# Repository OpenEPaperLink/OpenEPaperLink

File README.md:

# OpenEPaperLink

This is an alternative firmware and protocol for the multiple Electronic Shelf Labels. It can be used to set up E-Paper tags and supply them with content.

The software in this project consists of two parts: Accesspoint-firmware and Tag firmware.
Additionally, there are various hardware designs for accesspoints and flasher-interfaces to program the tags, preferably using programming jigs

>[!Note]
>Please refer to the [Wiki](https://github.com/jjwbruijn/OpenEPaperLink/wiki) for the latest information.
>
>Much of this README is now obsolete, but it has been retained for historical reference.
>
>For example the use of tags as RF coprocessors is no longer supported.
 
## Aims
- Low power (currently around 9µA with a minimum of 40 second latency)
- Even lower power when there's no AP around
- Low latency (tags can check for new data every 40 seconds)
- High transfer speeds - It can do about 5kbyte/s in favorable RF conditions. This allows for lower power
- RF-friendly - We don't need to acknowledge EVERY packet, and we don't need to transfer data we already have

## What is required to set up OpenEPaperLink

On the [Wiki](https://github.com/jjwbruijn/OpenEPaperLink/wiki) there is a ton of information regarding all kinds of tags and building the access points.

The entire setup requires a few tags and an ESP32. A tag is used as an 802.15.4 radio for the ESP32. You'll need a ZBS_Flasher in order to flash the tags. Using the 'mac' option on ZBS_Flasher makes sure a tag flashed with a custom firmware has a valid mac address; it uses the stock mac address assigned to the tag if it hasn't been flashed before. If you want to set it yourself, you can edit the mac address in the infopage.

You can hook the AP tag up to the ESP32 with mod wires or a flex PCB. The esp will flash the AP firmware to the Tag automatically. In some cases, a power off/on cycle is required. Please check the serial console output for status information.

After programming the ESP32, make sure to also program the filesystem. This will upload the 'data' folder to the ESP32, with the webinterface.

## OpenEPaperLink Parts and links
* [Mini AP](https://github.com/OpenEPaperLink/Hardware/tree/main/OpenEPaperLink%20Mini%20AP)
* [Combined Flasher and AP](https://github.com/OpenEPaperLink/Hardware/tree/main/OpenEPaperLink%20AP%20and%20Flasher)
* [ATC1441's ZBS flasher page](https://github.com/atc1441/ZBS_Flasher)
* [Tags specs](https://github.com/jjwbruijn/OpenEPaperLink/wiki#tags)
* [Tags troubleshooting](https://github.com/jjwbruijn/OpenEPaperLink/wiki/Troubleshooting-Tags)

## The protocol explained
- The tag checks in with the AP every 40+ seconds. Actual check-in interval is highly dependent on RF conditions, or if the AP tells the tag to delay the next check-in
- The AP holds a list with tag MACs that have pending transfers.
- If a tag checks in, the AP replies with either no data, or information about a pending transfer
- The tag checks if this information is already downloaded to EEPROM, or is already displayed. If this is the case, the transfer is immediately cancelled by issuing a 'transfer complete' packet to the AP.
- The tag then proceeds to request data in 'blocks' of 4096 bytes. The AP responds with an ACK on the request, and specifies how long it will take to gather the data. The tag sleeps until the AP will send the data
- The AP requests its block-buffer to be filled by the ESP32, specifying MD5 and blockID
- Datablock is sent by the AP, which will take about 42 packets for a full block. The tag will keep track of which blocks it has seen
- After a block has been received with missing parts, the tag will request the same block, with a bitmask of blocks that are missing
- The AP responds with the parts as requested by the tag. If there aren't too many blocks requested, the AP will fill the block with duplicate parts, to increase the chance of a successful transmission
- After a full block has been received, the tag will do a simple checksum over all received data. If the checksum matches, the 4K of data is stored in EEPROM storage for later use
- The tag will now either request the next block, or do a full re-request if the checksum failed
- If all blocks are received, the tag will send a 'transfer complete'. 
- The AP will report the completed transfer to the ESP32, and removes the pendingData for this transfer from the queue

## Known issues:
- Some tags work better as APs than others. Your range may suck. The boards on these tags are tiny and fragile. For instance, a dab of hot-glue on a board is enough to warp it pretty severely, and will damage the components that are soldered on there. Reportedly, segmented-display Solum tags work well. 

## Hints and excuses:
- There is no warranty whatsoever. Nothing. Not implied or otherwise suggested. This code isn't fit for anything. Please don't use this code to do nasty things.
- Do a ```make clean``` between buildings for different boards. It really helps!
- This repo builds on SDCC 4.2.0 for Linux. Different SDCC versions can behave VERY differently.  Source sdcc/setup.sh to setup build a local copy and use it for compiling.
- We are happy and honored to see your pull requests! But please, no code/indent style changes :)

## Credits
### Large parts of this repo are based on code written by, and wouldn't be possible without the hard work of:
- dmitry.gr
- atc1441

Hats off to these legends!
 
## Automated Builds
- After a PR gets merged to the main branch, the changed code will be compiled.
- On release, files are added to enable OTA

## License
[Creative Commons Attribution-NonCommercial-ShareAlike 4.0 International (CC BY-NC-SA 4.0)](https://creativecommons.org/licenses/by-nc-sa/4.0/)

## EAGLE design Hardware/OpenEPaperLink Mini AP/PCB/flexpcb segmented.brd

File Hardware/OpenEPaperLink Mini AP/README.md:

# OpenEPaperLink Mini-AP #

A small OpenEPaperLink AP, using an ESP32-S2 and a segmented tag

* [How to build one](https://github.com/jjwbruijn/OpenEPaperLink/blob/master/Hardware/OpenEPaperLink%20Mini%20AP/Building.md)

* [How to use one](https://github.com/jjwbruijn/OpenEPaperLink/blob/master/Hardware/OpenEPaperLink%20Mini%20AP/Getting%20Started.md)

* [Case](https://github.com/jjwbruijn/OpenEPaperLink/tree/master/Hardware/OpenEPaperLink%20Mini%20AP/Case)
                                                                                                                                                                                                                                                                                                                                                        
* [PCB](https://github.com/jjwbruijn/OpenEPaperLink/tree/master/Hardware/OpenEPaperLink%20Mini%20AP/PCB)

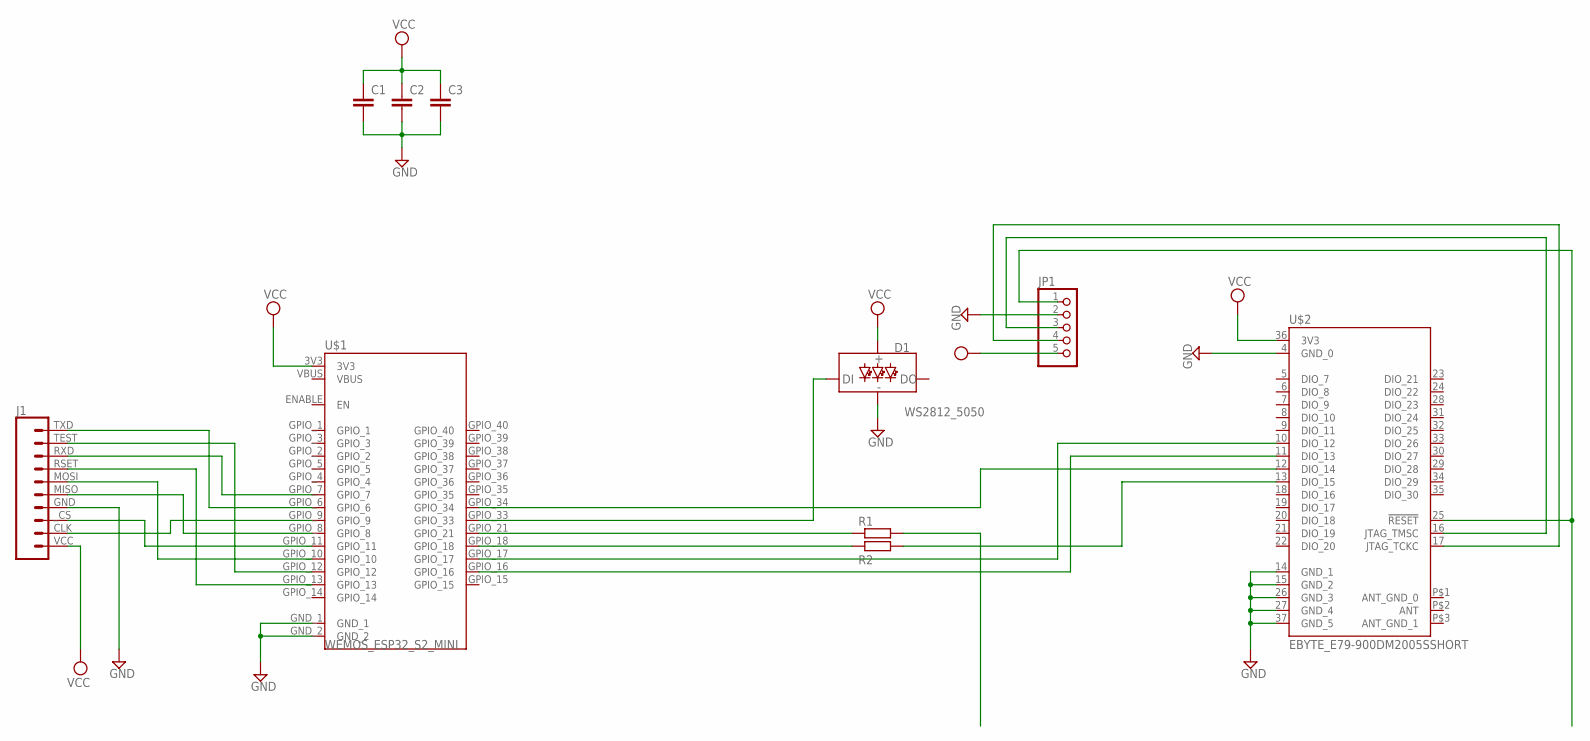
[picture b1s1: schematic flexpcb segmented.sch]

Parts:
C1, C2, C3: C-EUC1206; C1206
D1: WS2812_5050; WS2812-5X5-4PIN
J1: SOLUM_ZBS_DEBUGSEGMENTED_DISPLAY; SOLUM_ZBS_DEBUG_SEG
JP1: PINHD-1X55X2MM; 1_05X2MM
R1, R2: R-EU_R0805; R0805
U$1: WEMOS_ESP32_S2_MINI
U$2: EBYTE_E79-900DM2005SSHORT; EBYTE_E79-900DM2005S_PARTIAL

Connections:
ANT: U$2.P$2 (ANT)
ANT_GND_0: U$2.P$1 (ANT_GND_0)
ANT_GND_1: U$2.P$3 (ANT_GND_1)
GND: C1.2, C2.2, C3.2, D1.GND, J1.GND (4), JP1.2, U$1.GND_1, U$1.GND_2, U$2.4 (GND_0), U$2.14 (GND_1), U$2.15 (GND_2), U$2.26 (GND_3), U$2.27 (GND_4), U$2.37 (GND_5)
unnamed: JP1.1, U$2.25 (!RESET)
unnamed: R1.1, U$1.GPIO_21
unnamed: R2.2, U$2.13 (DIO_15)
unnamed: R2.1, U$1.GPIO_18
unnamed: U$1.GPIO_34, U$2.12 (DIO_14)
unnamed: U$1.GPIO_16, U$2.11 (DIO_13)
unnamed: U$1.GPIO_17, U$2.10 (DIO_12)
unnamed: D1.DI, U$1.GPIO_33
unnamed: JP1.3, U$2.16 (JTAG_TMSC)
unnamed: JP1.4, U$2.17 (JTAG_TCKC)
unnamed: J1.TEST (9), U$1.GPIO_12
unnamed: J1.RSET (7), U$1.GPIO_13
unnamed: J1._CS (3), U$1.GPIO_11
unnamed: J1.MOSI (6), U$1.GPIO_10
unnamed: J1.CLK (2), U$1.GPIO_9
unnamed: J1.RXD (8), U$1.GPIO_7
unnamed: J1.TXD (10), U$1.GPIO_6
unnamed: J1.MISO (5), U$1.GPIO_8
VBUS: U$1.VBUS
VCC: C1.1, C2.1, C3.1, D1.VCC, J1.VCC (1), JP1.5, U$1.3V3, U$2.36 (3V3)

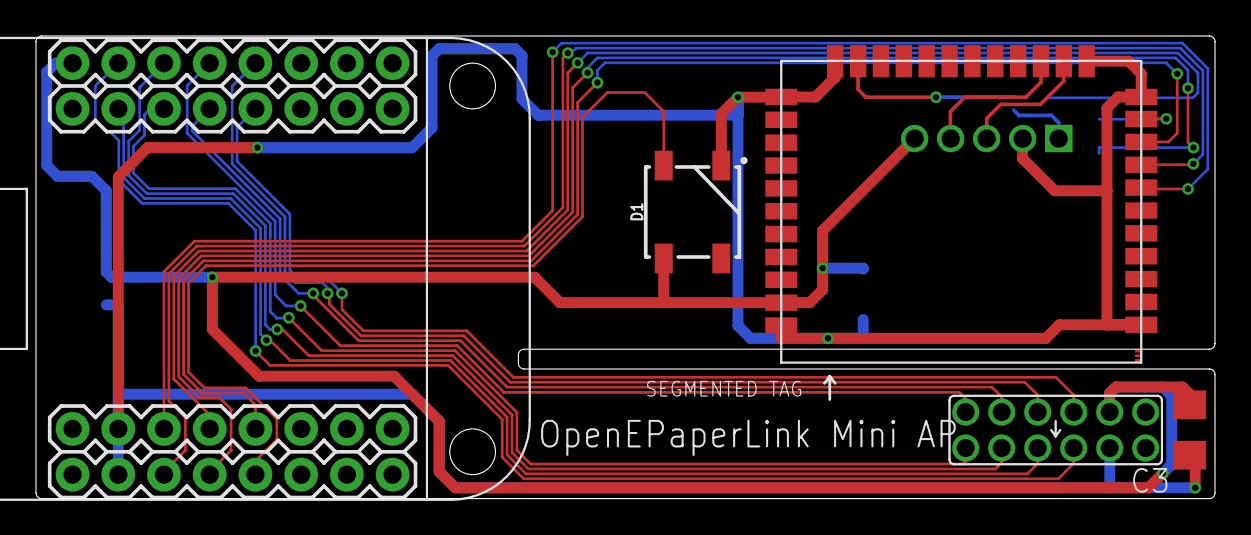
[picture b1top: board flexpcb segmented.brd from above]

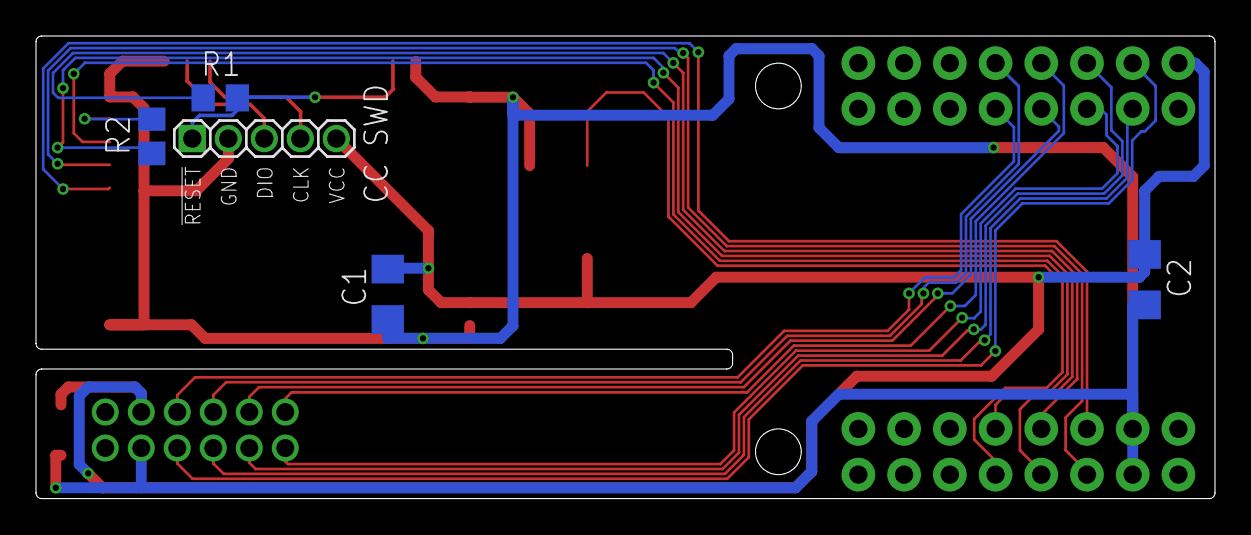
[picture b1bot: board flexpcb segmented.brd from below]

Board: 2 copper layers, 65.5 x 25.7 mm, 10 parts (5 on the bottom side), 20 nets.

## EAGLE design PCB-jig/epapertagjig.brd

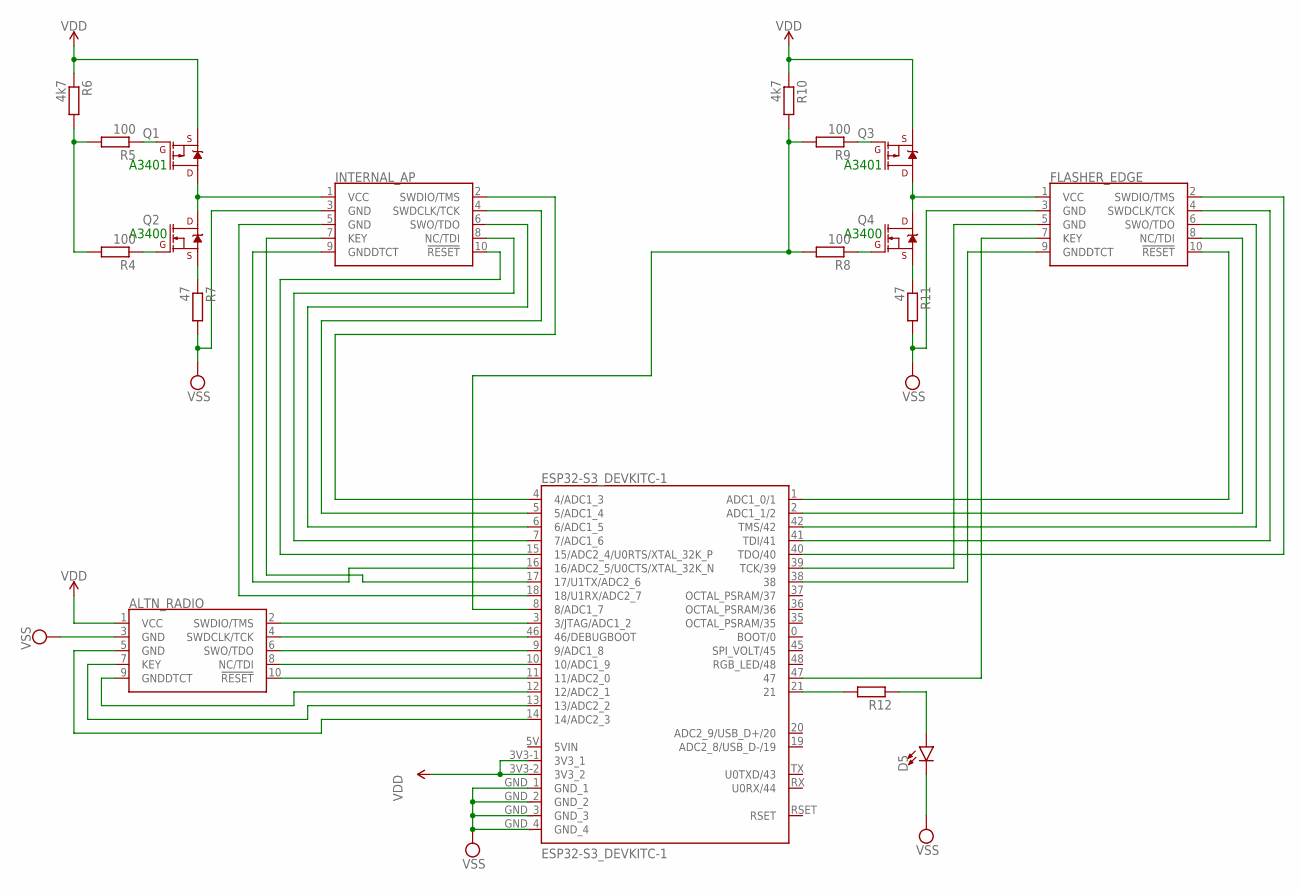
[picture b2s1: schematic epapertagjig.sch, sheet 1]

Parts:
ALTN_RADIO: JTAG; 2X5-SMD-1.27MM
D5: LED1206; LED-1206
FLASHER_EDGE: CORTEX_JTAG_DEBUG_PTH; 2X5-PTH-1.27MM
INTERNAL_AP: JTAG; 2X5-SMD-1.27MM
J9: ESP32-S3_DEVKITC-1
Q1, Q3: 1.1A/60V/600mΩ; SOT23-3
Q2, Q4: 5.8A/30V/35mΩ; SOT23-3
R4, R5, R8, R9: 100; R1206
R6, R10: 4k7; R1206
R7, R11: 47; R1206
R12: R-EU_R1206; R1206

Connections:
unnamed: INTERNAL_AP.1 (VCC), Q1.3 (D), Q2.3 (D)
unnamed: Q2.2 (S), R7.1
unnamed: R4.2, R5.2, R6.2
unnamed: Q2.1 (G), R4.1
unnamed: Q1.1 (G), R5.1
unnamed: FLASHER_EDGE.1 (VCC), Q3.3 (D), Q4.3 (D)
unnamed: J9.8 (8/ADC1_7), R8.2, R9.2, R10.2
unnamed: Q4.1 (G), R8.1
unnamed: Q3.1 (G), R9.1
unnamed: Q4.2 (S), R11.1
unnamed: INTERNAL_AP.5 (GND), J9.18 (18/U1RX/ADC2_7)
unnamed: INTERNAL_AP.9 (GNDDTCT), J9.16 (16/ADC2_5/U0CTS/XTAL_32K_N)
unnamed: INTERNAL_AP.10 (!RESET), J9.15 (15/ADC2_4/U0RTS/XTAL_32K_P)
unnamed: INTERNAL_AP.8 (NC/TDI), J9.7 (7/ADC1_6)
unnamed: INTERNAL_AP.6 (SWO/TDO), J9.6 (6/ADC1_5)
unnamed: INTERNAL_AP.4 (SWDCLK/TCK), J9.5 (5/ADC1_4)
unnamed: INTERNAL_AP.2 (SWDIO/TMS), J9.4 (4/ADC1_3)
unnamed: FLASHER_EDGE.6 (SWO/TDO), J9.42 (TMS/42)
unnamed: FLASHER_EDGE.10 (!RESET), J9.1 (ADC1_0/1)
unnamed: FLASHER_EDGE.8 (NC/TDI), J9.2 (ADC1_1/2)
unnamed: FLASHER_EDGE.4 (SWDCLK/TCK), J9.41 (TDI/41)
unnamed: FLASHER_EDGE.2 (SWDIO/TMS), J9.40 (TDO/40)
unnamed: ALTN_RADIO.2 (SWDIO/TMS), J9.3 (3/JTAG/ADC1_2)
unnamed: ALTN_RADIO.4 (SWDCLK/TCK), J9.46 (46/DEBUGBOOT)
unnamed: ALTN_RADIO.6 (SWO/TDO), J9.9 (9/ADC1_8)
unnamed: ALTN_RADIO.8 (NC/TDI), J9.10 (10/ADC1_9)
unnamed: ALTN_RADIO.10 (!RESET), J9.11 (11/ADC2_0)
unnamed: ALTN_RADIO.9 (GNDDTCT), J9.12 (12/ADC2_1)
unnamed: ALTN_RADIO.7 (KEY), J9.13 (13/ADC2_2)
unnamed: ALTN_RADIO.5 (GND), J9.14 (14/ADC2_3)
unnamed: FLASHER_EDGE.5 (GND), J9.39 (TCK/39)
unnamed: FLASHER_EDGE.9 (GNDDTCT), J9.38
unnamed: FLASHER_EDGE.7 (KEY), J9.47
unnamed: INTERNAL_AP.7 (KEY), J9.17 (17/U1TX/ADC2_6)
unnamed: J9.21, R12.2
unnamed: D5.A, R12.1
VDD: ALTN_RADIO.1 (VCC), J9.3V3-1 (3V3_1), J9.3V3-2 (3V3_2), Q1.2 (S), Q3.2 (S), R6.1, R10.1
VSS: ALTN_RADIO.3 (GND), D5.C, FLASHER_EDGE.3 (GND), INTERNAL_AP.3 (GND), J9.GND_1, J9.GND_2, J9.GND_3, J9.GND_4, R7.2, R11.2

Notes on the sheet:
A3401
A3400

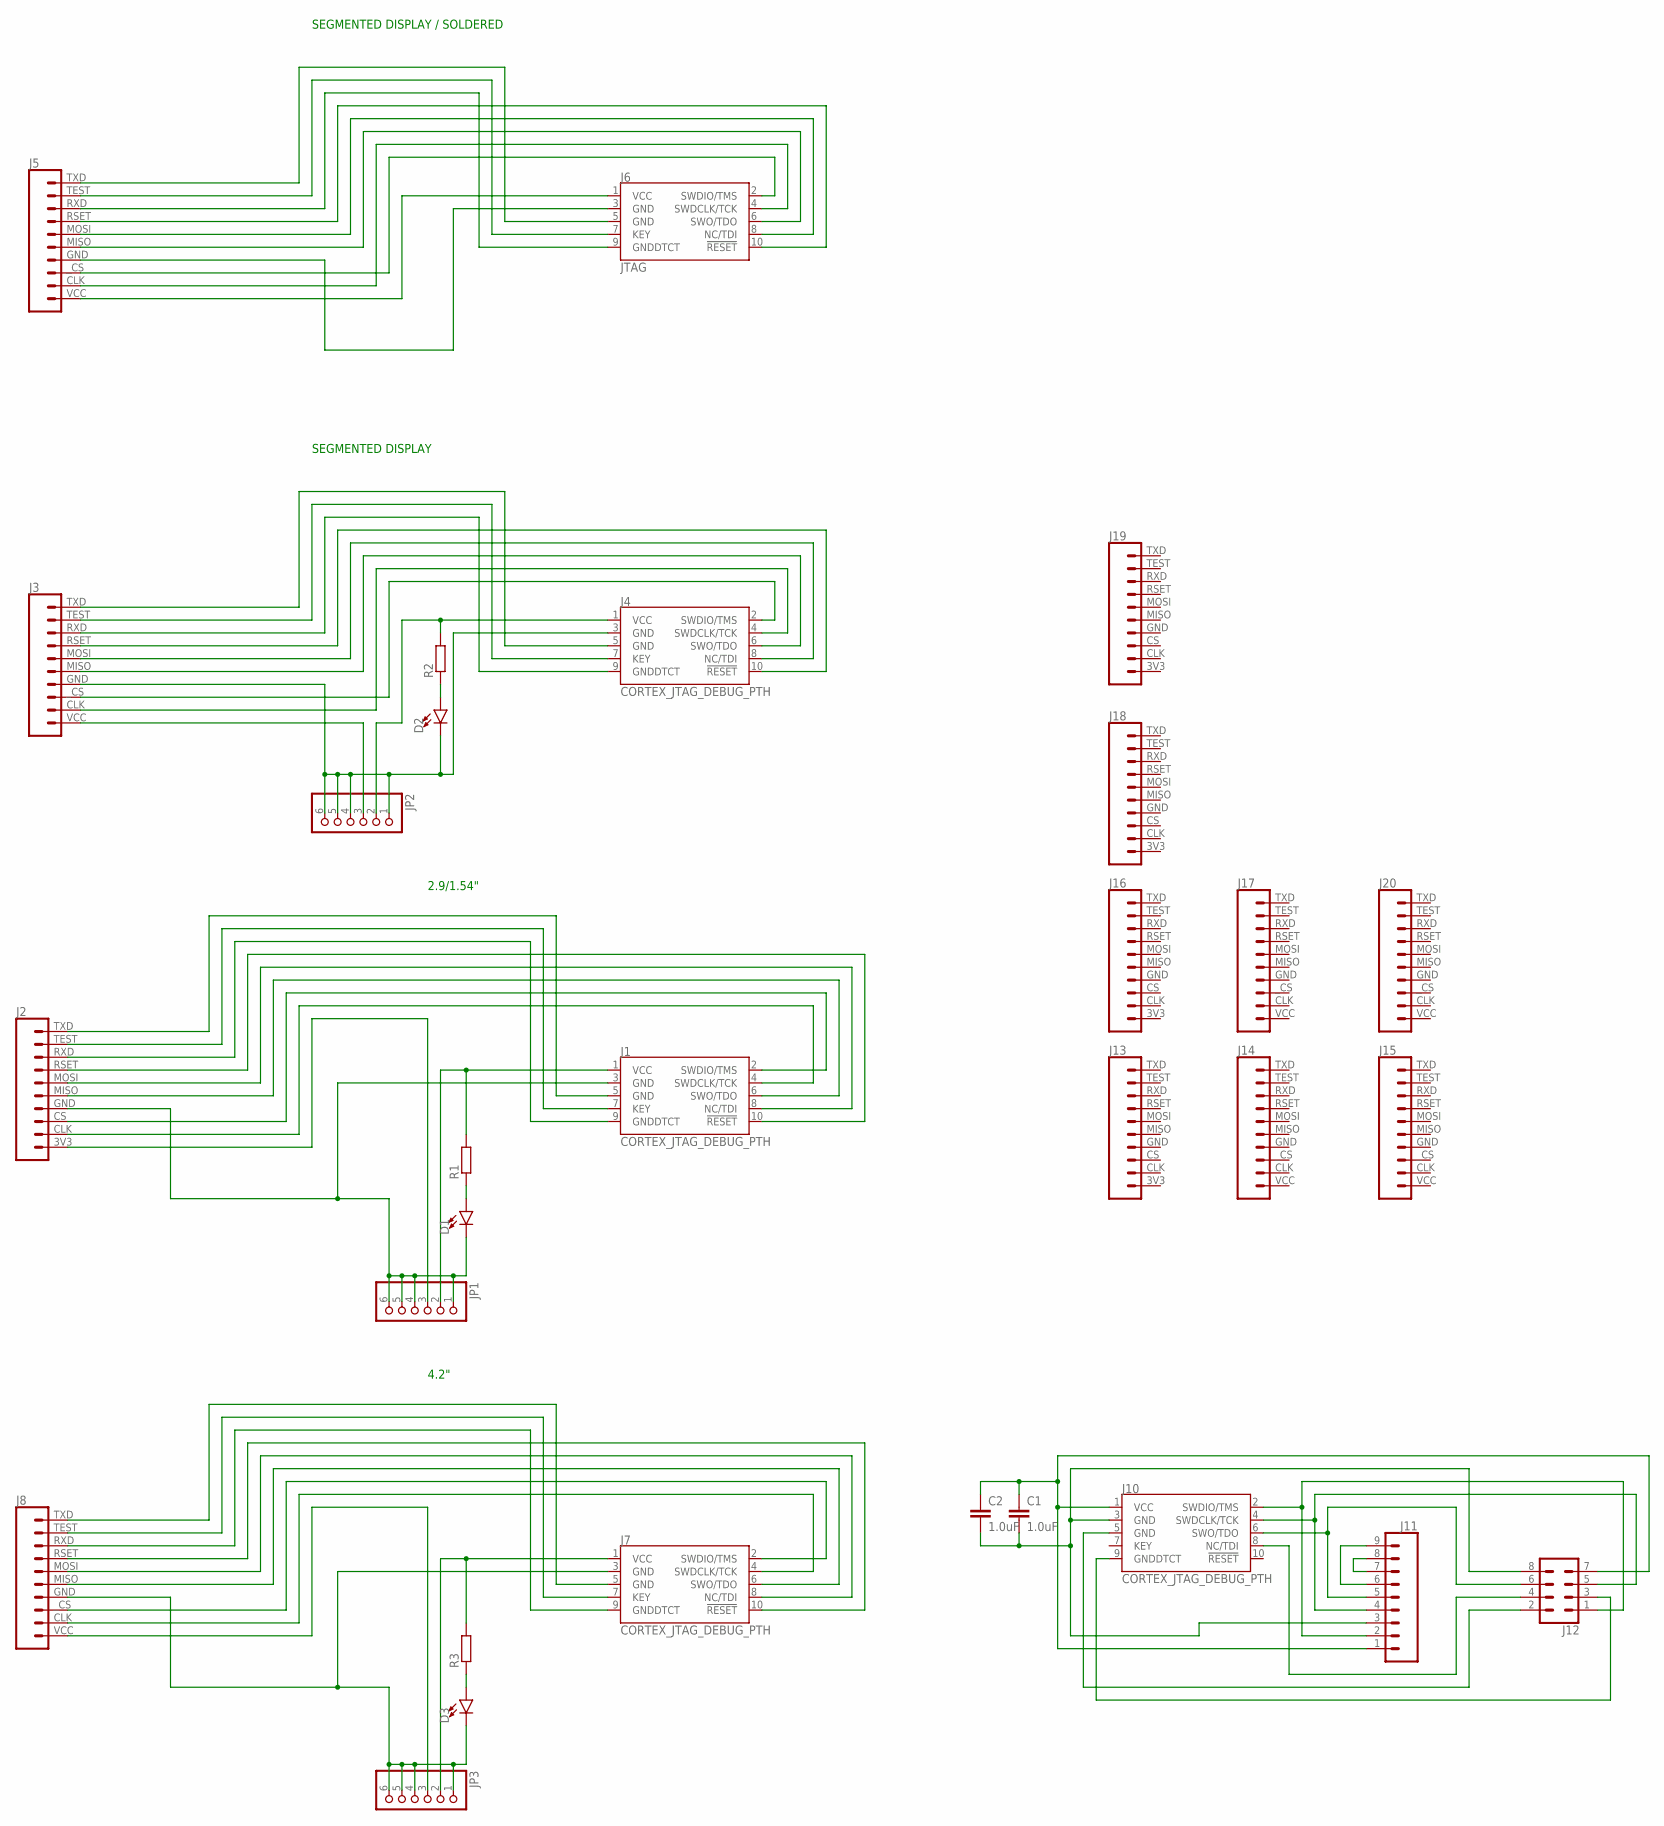
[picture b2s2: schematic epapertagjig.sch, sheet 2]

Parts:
C1, C2: 1.0uF; 1206
D1, D2, D3: LED1206; LED-1206
J1, J4, J7, J10: CORTEX_JTAG_DEBUG_PTH; 2X5-PTH-1.27MM
J2, J13, J16, J18, J19: SOLUM_ZBS_DEBUG
J3, J5, J14, J17: SOLUM_ZBS_DEBUGSEGMENTED_DISPLAY; SOLUM_ZBS_DEBUG_SEG
J6: JTAG; 2X5-SMD-1.27MM
J8, J15, J20: SOLUM_ZBS_DEBUGSOLUM_ZBS_DEBUG_4.2; SOLUM_ZBS_DEBUG_4.2
J11: CONN_09; 1X09
J12: CONN_04X2; 2X4
JP1, JP2, JP3: PINHD-1X6/90; 1X06/90
R1, R2, R3: R-EU_R1206; R1206

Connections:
3V1: J8.VCC (1), JP3.3
3V3: J2.3V3 (1), JP1.3
GND: D1.C, J1.3 (GND), J2.GND (4), JP1.1, JP1.4, JP1.5, JP1.6
GND1: J5.GND (4), J6.3 (GND)
GND2: D2.C, J3.GND (4), J4.3 (GND), JP2.1, JP2.4, JP2.5, JP2.6
GND3: D3.C, J7.3 (GND), J8.GND (4), JP3.1, JP3.4, JP3.5, JP3.6
unnamed: D2.A, R2.1
unnamed: D1.A, R1.1
unnamed: D3.A, R3.1
unnamed: J4.1 (VCC), JP2.2, R2.2
unnamed: J1.4 (SWDCLK/TCK), J2.CLK (2)
unnamed: J1.2 (SWDIO/TMS), J2.CS (3)
unnamed: J1.6 (SWO/TDO), J2.MISO (5)
unnamed: J3._CS (3), J4.2 (SWDIO/TMS)
unnamed: J1.8 (NC/TDI), J2.MOSI (6)
unnamed: J1.10 (!RESET), J2.RSET (7)
unnamed: J1.9 (GNDDTCT), J2.RXD (8)
unnamed: J1.7 (KEY), J2.TEST (9)
unnamed: J1.5 (GND), J2.TXD (10)
unnamed: J3.CLK (2), J4.4 (SWDCLK/TCK)
unnamed: J3.MISO (5), J4.6 (SWO/TDO)
unnamed: J3.MOSI (6), J4.8 (NC/TDI)
unnamed: J3.RSET (7), J4.10 (!RESET)
unnamed: J3.VCC (1), JP2.3
unnamed: J3.RXD (8), J4.9 (GNDDTCT)
unnamed: J3.TEST (9), J4.7 (KEY)
unnamed: J3.TXD (10), J4.5 (GND)
unnamed: J7.4 (SWDCLK/TCK), J8.CLK (2)
unnamed: J5._CS (3), J6.2 (SWDIO/TMS)
unnamed: J5.CLK (2), J6.4 (SWDCLK/TCK)
unnamed: J5.MISO (5), J6.6 (SWO/TDO)
unnamed: J5.MOSI (6), J6.8 (NC/TDI)
unnamed: J5.RSET (7), J6.10 (!RESET)
unnamed: J5.VCC (1), J6.1 (VCC)
unnamed: J5.RXD (8), J6.9 (GNDDTCT)
unnamed: J5.TEST (9), J6.7 (KEY)
unnamed: J5.TXD (10), J6.5 (GND)
unnamed: J7.2 (SWDIO/TMS), J8._CS (3)
unnamed: J7.6 (SWO/TDO), J8.MISO (5)
unnamed: J7.8 (NC/TDI), J8.MOSI (6)
unnamed: J7.10 (!RESET), J8.RSET (7)
unnamed: J7.9 (GNDDTCT), J8.RXD (8)
unnamed: J7.7 (KEY), J8.TEST (9)
unnamed: J7.5 (GND), J8.TXD (10)
unnamed: C1.1, C2.1, J10.1 (VCC), J11.1, J12.7
unnamed: J11.7, J11.8
unnamed: C1.2, C2.2, J10.3 (GND), J11.3, J12.8
unnamed: J11.6, J11.9
unnamed: J10.6 (SWO/TDO), J11.5, J12.6
unnamed: J10.4 (SWDCLK/TCK), J11.4, J12.5
unnamed: J10.2 (SWDIO/TMS), J11.2, J12.1
unnamed: J10.8 (NC/TDI), J12.4
unnamed: J10.5 (GND), J12.2
unnamed: J10.9 (GNDDTCT), J12.3
V_IN: J1.1 (VCC), JP1.2, R1.2
V_IN1: J7.1 (VCC), JP3.2, R3.2

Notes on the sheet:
SEGMENTED DISPLAY
2.9/1.54"
SEGMENTED DISPLAY / SOLDERED
4.2"

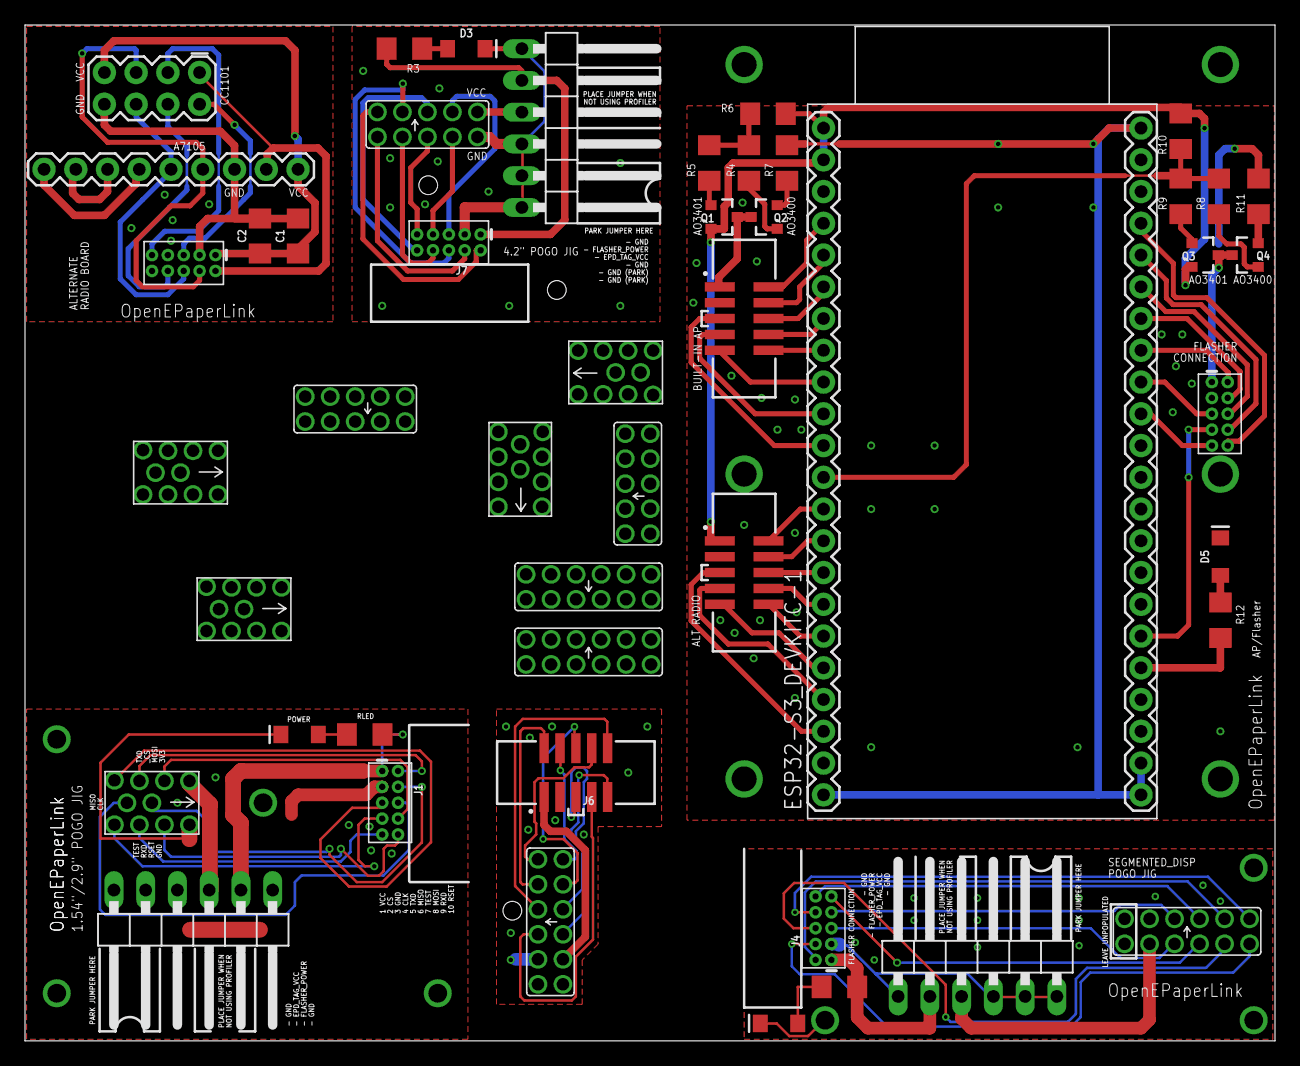
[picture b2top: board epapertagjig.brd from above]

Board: 2 copper layers, 100.0 x 81.3 mm, 48 parts (0 on the bottom side), 94 nets.

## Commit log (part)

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2025-03-24 Avoid error message log print when parsers.json is missing
2025-03-24 Add Ethernet support
    The ethernet support allows to make the network/internet connection
    via LAN cable instead of WiFi. LAN is preferred, if a LAN cable is
    connected and a valid IP configuration via DHCP can be obtained, WiFi
    is switched off. If the LAN cable is disconnected, a fall back to
    WiFi is done.
    Use those defines in platform.ini for PHY settings:
2025-03-24 Add OpenEPaperLink_ESP32-PoE-ISO_AP to release build
2025-03-25 Added support for Elecrow C6 wireless module.
2025-03-25 Added optional (compile time) debug logging to C6 & H2.
2025-03-25 Added support for Elcrow Advanced 2.8" AP.
2025-03-25 Added E5.json for Elcrow Advanced 2.8" AP.
2025-03-26 Add new AP hardware support OpenEPaperLink_ESP32-PoE-ISO_AP (#431)
    * Fix filesystem mutex handling
    This fixes the re-initialization of the filesystem mutex when the dyn storage
    module is reinitialized. Using xSemaphoreCreateMutex would cause a memory leak
    when the begin function is called multiple times and a semaphore leakage could
    be caused by the re-initialization of the global fsMutex variable while the
    semaphore is taken.
2025-03-27 more robust extended sleep time and 'no updates between' handling
2025-03-27 stability improvements in C6 flashing
2025-03-28 OTA update tweaks
2025-03-31 Added 2.7" tagtype
2025-03-31 Delete resources/tagtypes/49.json
    47 already exists
2025-04-03 new tagtype M3 2.7" and M3 11.6" layouts and other tweaks
2025-04-05 fixes crash when dayahead data is unavailable
2025-04-05 Add OpenEPaperLink_Nano_TLSR_C6 and ESP32_S3_16_8_4inch_AP to automatic builds
2025-04-06 Added a Clock mode as content type
2025-04-12 added sunrise/sunset/moon phase to date display
2025-04-14 Added 5.81" BWR V2 because of UC Variant needs rotated image
2025-04-15 Enable zlib_compression support.
2025-04-27 css: fallback to 'monospace' for AP log view
    Log view on firmware update page was not printed using fixed width font on my system.
    Now it is.
    Closes: #460
2025-04-27 css: fallback to 'monospace' for AP log view (#461)
    Log view on firmware update page was not printed using fixed width font on my system.
    Now it is.
    Closes: #460
2025-05-18 Added more TagTypes
2025-05-19 Edited 800x480 Template
2025-05-26 Added more advanced Json template demo
2025-05-27 Create 29.json
    Added 2.4" BWRY definition
2025-05-29 TagType Update
2025-06-05 Added Chroma 74 BWR binaries version 0014.
2025-06-14 Button 3
2025-06-14 Button 3 (#473)
2025-06-14 fix build of serialap module
    wifimanager need to be used to read local IP address.
2025-06-14 fix build of serialap module (#475)
    wifimanager need to be used to read local IP address.
2025-07-06 Add configurable period for Google Calendar tags
2025-07-18 Chroma29 v0015: fix high battery current on some tags (#459).
2025-07-19 Updated Chroma29 entry in tagotaversions.json.
2025-07-20 Don't delay content generate when shorten latency is enabled and user is connected.
2025-08-01 Adding support for Waveshare ESP32-S3-ETH
2025-09-06 Ability to update time without requiring Internet Access
2025-09-11 Added DarkMode to AP Gui
2025-09-12 Also updated the .gz files
2025-09-15 Update painter.js
    Added more font sizes to support things like a single emoji on T-Panel and larger displays.
2025-09-15 Update main.js
    Adding support for cased versions of jpg and jpeg.
2025-10-17 New firmware hash found for ST-GR2900N.
2025-10-20 Feat: dayahead fixes and improvements
2025-10-20 Feat: dayahead fixes and improvements (#516)
2025-10-21 Add definitions for more now-known Solum BWRY tags
    https://github.com/OpenEPaperLink/Tag_FW_EFR32xG22/issues/11
2025-10-28 Add 11.6" BWRY and fix previous BWRY definitions
2025-10-30 Added BWRY Preview
2025-11-06 Added support for ts_option to provide finer control of time stamps. 1. Fixed time stamp overlap on weather forecast content on 2.9" tags. 2. Fixed time stamp overlap on AP info screen on 160x80 TFT 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
2025-11-16 Fixed the pin order for the display on the ESP32_S3_16_8_4inch_AP
2025-11-16 Updated the WebFiles as well
2025-11-20 Feature Wireguard Addon
2025-11-20 Feature Wireguard Addon remove README Files
2025-11-20 fix patch Wireguard-Library ciniml/WireGuard-ESP32@^0.1.5 add methode shutdown_timer_only
2025-11-23 Fix WireGuard crashes with automatic library patch
2025-11-23 Remove legancy File patch_wireguard.py
2025-12-06 Allow to disable sleep mode
2025-12-07 Use correct base templates for BWRY variants
2025-12-09 Updated UseGhz setting
2025-12-11 Added M3 2.6" BW
2025-12-16 Add a user authentication
2025-12-16 Add compressed www files
2026-01-18 Added V2 ATC_BLE_OEPL Advertising Handling
2026-01-24 Add SPAGHETTI for ESP32-S3 16MB Flash 8MB RAM
    same as yelllow AP but without TFT config.
2026-02-04 Create 006C.json
    This is for Hanshow Pro 154Q-N, 200x200 tested and working for me. The Hardware ID 0006C is what ATC_BLE_OEPL_Image_Upload tells me when i read Display Settings.
2026-02-04 Rename 006C.json to 006G.json
2026-02-04 Rename 006G.json to 06F.json
    Ok, 06G is not a valid Hex, is 06F ok?
2026-02-04 Rename 06F.json to 64.json
2026-02-13 Added 4F for 2.6" BWRY M3.
2026-02-13 Add definition for M3 4.2 BWRY
    https://github.com/OpenEPaperLink/Shared_OEPL_Definitions/pull/5
    https://github.com/OpenEPaperLink/Tag_FW_EFR32xG22/pull/16
2026-02-19 sunrise sunset moon phase fix
2026-02-20 add warning
2026-02-23 Added 91.json for the EL016F6W4A M3 1.6" BWRY variant.
2026-02-27 Added 2.9 and 2.13 High Res
2026-03-04 Created new AP setup using the Lilygo T-Display-S3 board (#423)
    * Created new AP setup using the Lilygo T-Display-S3 board
    * Updated UseGhz setting
2026-03-05 Point to Wiki for EFR32 tag flashing info from Tag Flasher readme.md.
2026-03-06 Missed erase function (#549)
    * Update swd.h
    * Update swd.cpp
    * Update usbflasher.cpp
2026-03-11 Enhance NTP configuration with DHCP support
    Added function to check if NTP servers are provided via DHCP.
2026-03-13 Fix buffer size truncation for non-8-aligned image dimensions
    Integer division (w*h)/8 truncates when w*h is not a multiple of 8,
    allocating one byte too few. spr2color then writes past the end of
    the buffer, corrupting the heap. Use (w*h+7)/8 to round up correctly.
    Triggered by any tag whose width*height is not divisible by 8.
2026-03-13 Fix buffer size truncation for non-8-aligned image dimensions (#561)
    Integer division (w*h)/8 truncates when w*h is not a multiple of 8,
    allocating one byte too few. spr2color then writes past the end of
    the buffer, corrupting the heap. Use (w*h+7)/8 to round up correctly.
    Triggered by any tag whose width*height is not divisible by 8.
2026-03-19 Better HD150 5.83" Design
2026-03-19 Better HD150 5,83" Content design
2026-03-30 Swap color values for black and white
2026-04-22 Add GICisky 2.9" BWRY display support
    The new 2.9" GICisky tag (model byte 0x2E) advertises on BLE and shows
    in the tag list but never updates, because OEPL only knew the 3-color
    BWR variants and sends image data as a dual bitplane. This display
    expects a single bitplane with 2 bpp packed pixels where 00=Black,
    01=White, 10=Yellow, 11=Red, per the hass-gicisky reference library.
    - Map manufacturer byte 0x2E to new GICI_BLE_EPD_29_BWRY (0xBC).
2026-04-26 + cron syntax for update interval
2026-05-07 Add Wolink/Zhsunyco BLE ESL 2.13" BWRY support
    Adds an entirely new BLE ESL family alongside the existing GICisky and
    ATC paths. The 2.13" BWRY tag advertises with manufacturer ID 0xAABB
    and uses a Wolink/Zhsunyco protocol over BLE only:
    - 16-byte AES-128-CBC challenge/response auth (zero IV, PKCS#7 pad)
    - 238 B chunked image upload with 4 B little-endian offset header
    - Single-bitplane 2 bpp pixel layout, column-major, y-flipped
2026-05-28 WIP - image generation working with hard coded test data.
2026-06-01 Honor LED off setting for yellow AP activity pulse
    On `HAS_TFT` boards the radio activity pulse was hardcoded to full
    brightness, ignoring a configured-off LED. Gate it on `maxledbrightness`
    so brightness 0 keeps the LED dark while non-zero still pulses at full.
2026-06-01 Honor LED off setting for C6 radio activity LED
    The C6 co-processor pulses its own GPIO activity LED on radio traffic,
    independent of the host's `config.led`. Carry the LED on/off state in a
    new `flags` byte of the `espSetChannelPower` (`SCP>`) command so the C6
    silences it when the LED is disabled, and re-send `SCP>` on a LED-only
    config change so it applies without a reboot.
    The struct gains a byte, so the host and C6 firmware are now version
2026-06-01 Add compile.sh shell port of compile.ps1
2026-06-05 WIP - image generation working with hard coded data for 400x300, 640x385 and 800x480 with actual battery, temperature and RSSI values from tag.
2026-06-06 WIP working end to end with live data. 1. Replaced TestOWM.cpp with OwmWeather.cpp. 2. Added support for entering Owm API config to web gui.
2026-06-08 Fix crash when timestamps are enabled and LOAD_GFXFF is defined.
2026-06-13 Add virtual (simulated) tags for hardware-free testing
    Create virtual (simulated) tags in the web UI to develop and test the AP
    without physical e-paper hardware. A virtual tag reuses the real
    processDataReq / sendDataAvail pipeline, so the AP behaves and broadcasts
    (e.g. wakeupReason over /ws) exactly as it would for a real tag.
    - new module src/virtualtag.{cpp,h} and a persisted isVirtual flag on tagRecord
    - endpoints POST /vtag_create and /vtag_event, plus wsSendVirtualLed for the
2026-06-15 add support for Gicisky BWRY 2.9" ESL
2026-06-20 Persist virtual tag immediately on creation
    The periodic saveDB() only runs every few minutes, so a virtual tag
    created via /vtag_create was lost if the AP restarted or was power-cycled
    before the next periodic save. Save the tag DB right after creating it,
    matching how the other web tag operations persist their changes.
2026-06-22 Added better CC1310M3 Firmware SubGhz
2026-06-23 Added better CC1310M2 Firmware SubGhz

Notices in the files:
parts and their libraries:
SparkFun-Connectors: Licensing: Creative Commons ShareAlike 4.0 International - https://creativecommons.org/licenses/by-sa/4.0
